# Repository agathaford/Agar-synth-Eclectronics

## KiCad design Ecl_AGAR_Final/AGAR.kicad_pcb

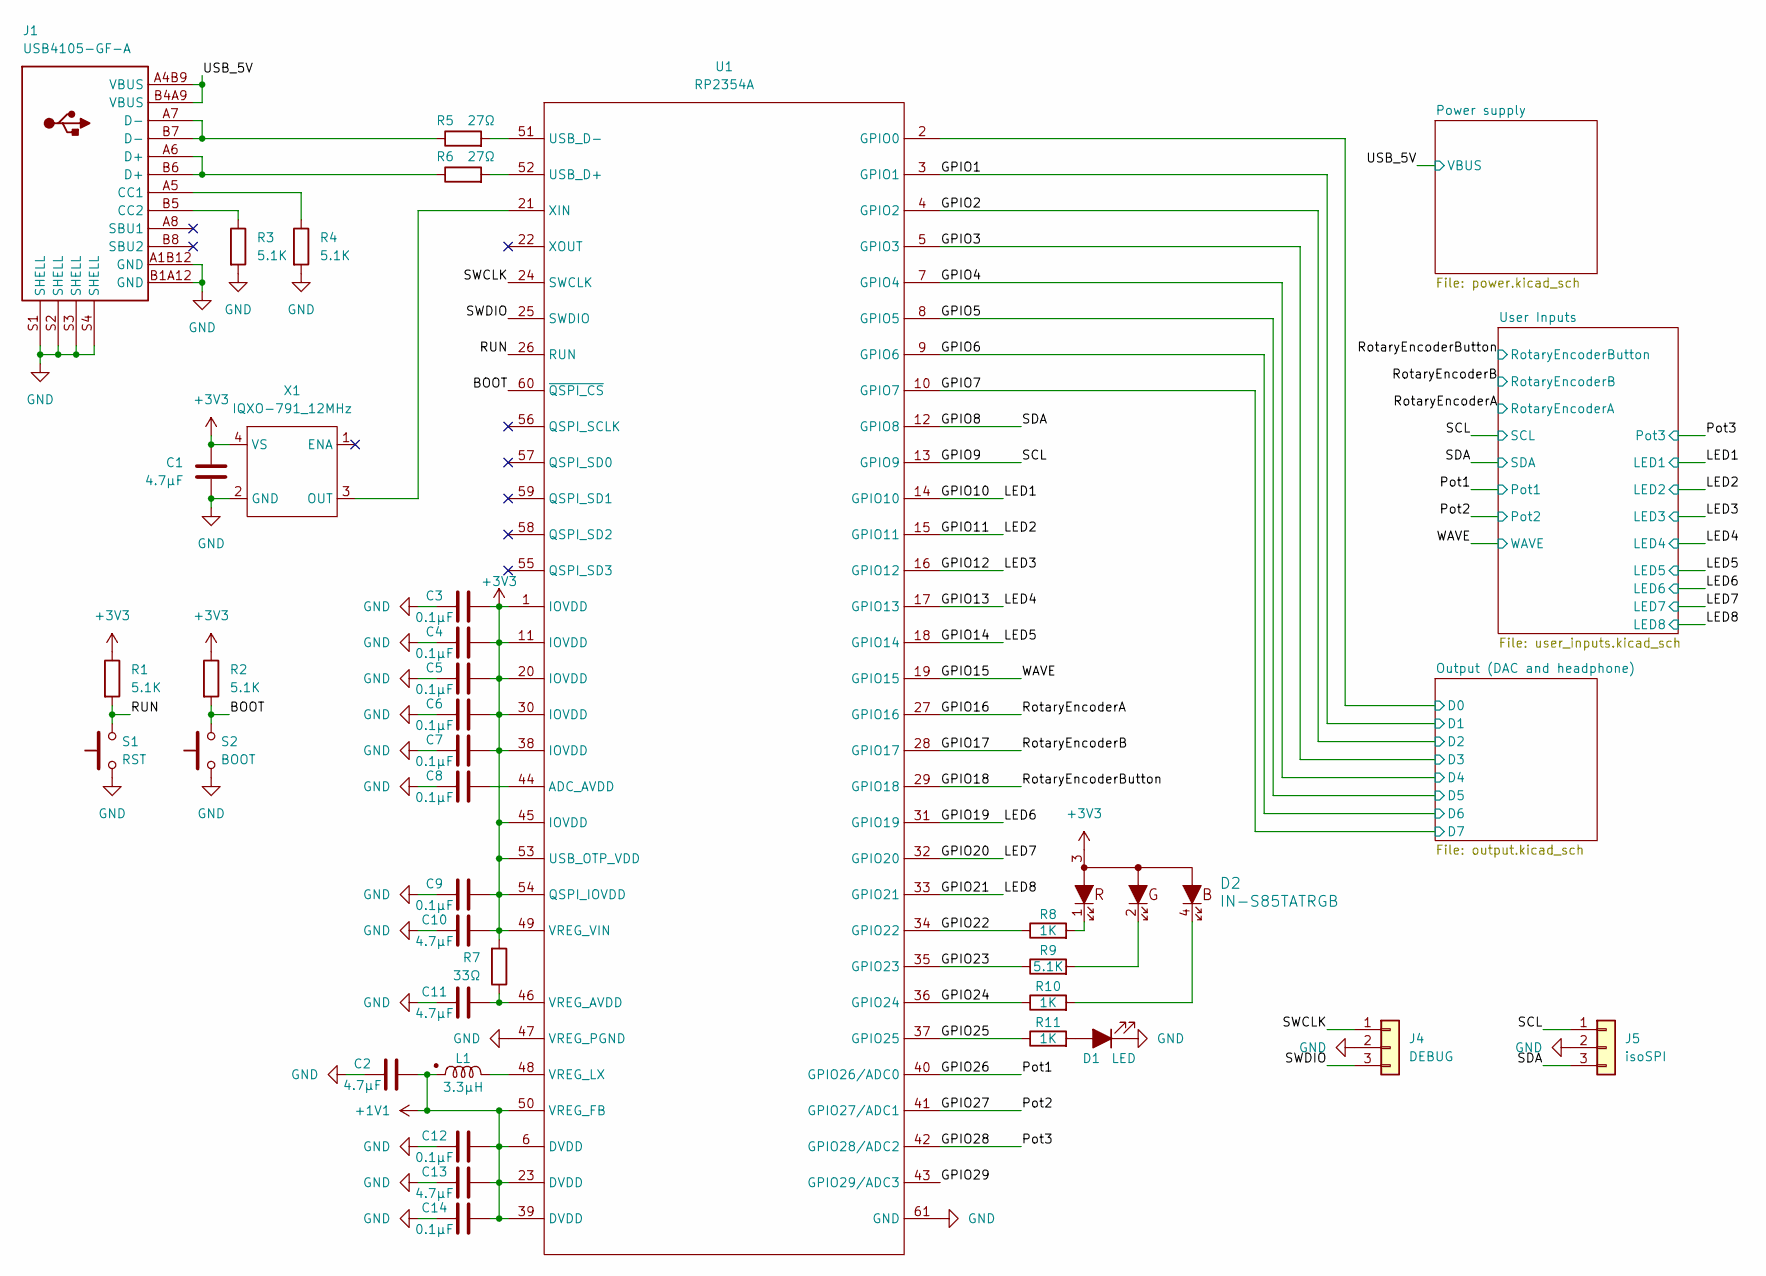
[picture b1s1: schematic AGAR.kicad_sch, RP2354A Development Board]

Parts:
C1, C2, C10, C11, C13: 4.7µF; C_0603_1608Metric
C3, C4, C5, C6, C7, C8, C9, C12, C14: 0.1µF; C_0603_1608Metric
D1: LED; LED_0805_2012Metric
D2: IN-S85TATRGB
J1: USB4105-GF-A
J4: DEBUG; PinHeader_1x03_P2.54mm_Vertical
J5: isoSPI; PinHeader_1x03_P2.54mm_Vertical
L1: 3.3µH; AOTA-B201610S3R3-101-T
R1, R2, R3, R4, R9: 5.1K; R_0603_1608Metric
R5, R6: 27Ω; R_0603_1608Metric
R7: 33Ω; R_0603_1608Metric
R8, R10, R11: 1K; R_0603_1608Metric
S1: RST; TL3301AFxxxxJ
S2: BOOT; TL3301AFxxxxJ
U1: RP2354A; RP2350A_QFN-60_EP_7.75x7.75_Pitch0.4mm
X1: IQXO-791_12MHz; WE-SPXO_IQXO-791

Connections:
+1V1: C2.2, C12.2, C13.2, C14.2, L1.1, U1.6 (DVDD), U1.23 (DVDD), U1.39 (DVDD), U1.50 (VREG_FB)
+3V3: C1.2, C3.2, C4.2, C5.2, C6.2, C7.2, C8.2, C9.2, C10.2, D2.3, R1.1, R2.1, R7.2, U1.1 (IOVDD), U1.11 (IOVDD), U1.20 (IOVDD), U1.30 (IOVDD), U1.38 (IOVDD), U1.44 (ADC_AVDD), U1.45 (IOVDD), U1.49 (VREG_VIN), U1.53 (USB_OTP_VDD), U1.54 (QSPI_IOVDD), X1.4 (VS); also elsewhere on the board
/BOOT: R2.2, S2.2, U1.60 (~QSPI_CS)
/GPIO1: U1.3 (GPIO1); also elsewhere on the board
/GPIO2: U1.4 (GPIO2); also elsewhere on the board
/GPIO3: U1.5 (GPIO3); also elsewhere on the board
/GPIO4: U1.7 (GPIO4); also elsewhere on the board
/GPIO5: U1.8 (GPIO5); also elsewhere on the board
/GPIO6: U1.9 (GPIO6); also elsewhere on the board
/GPIO7: U1.10 (GPIO7); also elsewhere on the board
/GPIO8: J5.3, U1.12 (GPIO8); also elsewhere on the board
/GPIO9: J5.1, U1.13 (GPIO9); also elsewhere on the board
/GPIO10: U1.14 (GPIO10); also elsewhere on the board
/GPIO11: U1.15 (GPIO11); also elsewhere on the board
/GPIO12: U1.16 (GPIO12); also elsewhere on the board
/GPIO13: U1.17 (GPIO13); also elsewhere on the board
/GPIO14: U1.18 (GPIO14); also elsewhere on the board
/GPIO15: U1.19 (GPIO15); also elsewhere on the board
/GPIO16: U1.27 (GPIO16); also elsewhere on the board
/GPIO17: U1.28 (GPIO17); also elsewhere on the board
/GPIO18: U1.29 (GPIO18); also elsewhere on the board
/GPIO19: U1.31 (GPIO19); also elsewhere on the board
/GPIO20: U1.32 (GPIO20); also elsewhere on the board
/GPIO21: U1.33 (GPIO21); also elsewhere on the board
/GPIO22: R8.1, U1.34 (GPIO22)
/GPIO23: R9.1, U1.35 (GPIO23)
/GPIO24: R10.1, U1.36 (GPIO24)
/GPIO25: R11.1, U1.37 (GPIO25)
/GPIO26: U1.40 (GPIO26/ADC0); also elsewhere on the board
/GPIO27: U1.41 (GPIO27/ADC1); also elsewhere on the board
/GPIO28: U1.42 (GPIO28/ADC2); also elsewhere on the board
/GPIO29: U1.43 (GPIO29/ADC3)
/Output (DAC and headphone)/D0: U1.2 (GPIO0); also elsewhere on the board
/RUN: R1.2, S1.2, U1.26 (RUN)
/SWCLK: J4.1, U1.24 (SWCLK)
/SWDIO: J4.3, U1.25 (SWDIO)
/USB_5V: J1.A4B9 (VBUS), J1.B4A9 (VBUS); also elsewhere on the board
GND: C1.1, C2.1, C3.1, C4.1, C5.1, C6.1, C7.1, C8.1, C9.1, C10.1, C11.1, C12.1, C13.1, C14.1, D1.1 (K), J1.A1B12 (GND), J1.B1A12 (GND), J1.S1 (SHELL), J1.S2 (SHELL), J1.S3 (SHELL), J1.S4 (SHELL), J4.2, J5.2, R3.2, R4.2, S1.1, S2.1, U1.47 (VREG_PGND), U1.61 (GND), X1.2 (GND); also elsewhere on the board
unnamed: D1.2 (A), R11.2
unnamed: D2.1, R8.2
unnamed: D2.2, R9.2
unnamed: D2.4, R10.2
unnamed: J1.A5 (CC1), R4.1
unnamed: J1.B5 (CC2), R3.1
unnamed: J1.A6 (D+), J1.B6 (D+), R6.1
unnamed: J1.A7 (D-), J1.B7 (D-), R5.1
unnamed: R6.2, U1.52 (USB_D+)
unnamed: R5.2, U1.51 (USB_D-)
unnamed: C11.2, R7.1, U1.46 (VREG_AVDD)
unnamed: L1.2, U1.48 (VREG_LX)
unnamed: U1.21 (XIN), X1.3 (OUT)

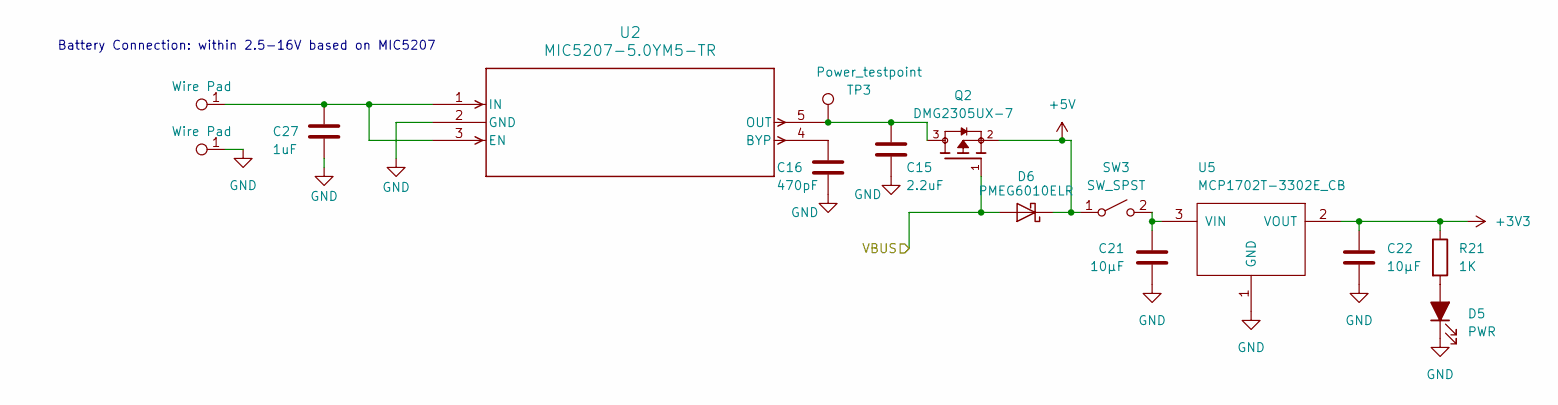
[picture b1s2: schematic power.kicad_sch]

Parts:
C15: 2.2uF; C_0603_1608Metric
C16: 470pF; C_0603_1608Metric
C21, C22: 10µF; C_0603_1608Metric
C27: 1uF; C_0603_1608Metric
D5: PWR; LED_0805_2012Metric
D6: PMEG6010ELR; Nexperia_CFP3_SOD-123W
Q2: DMG2305UX-7; DMG2305UX_7_SOT-23_DIO; MPN DMG2305UX-7
R21: 1K; R_0603_1608Metric
SW3: SW_SPST; SLW-1276864_CUD
TP3: Power_testpoint; TestPoint_Pad_D3.0mm
U2: MIC5207-5.0YM5-TR; SOT-23-5_M5_MCH
U5: MCP1702T-3302E_CB; SOT95P255X145-3N
WirePad13, WirePad14: Wire Pad

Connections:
+3V3: C22.1, R21.1, U5.2 (VOUT); also elsewhere on the board
+5V: D6.1 (K), Q2.2, SW3.1 (A); also elsewhere on the board
/USB_5V: D6.2 (A), Q2.1; also elsewhere on the board
GND: C15.2, C16.2, C21.1, C22.2, C27.2, D5.1 (K), U2.2 (GND), U5.1 (GND), WirePad14.1 (1_1); also elsewhere on the board
unnamed: D5.2 (A), R21.2
unnamed: C21.2, SW3.2 (B), U5.3 (VIN)
unnamed: C16.1, U2.4 (BYP)
unnamed: C27.1, U2.1 (IN), U2.3 (EN), WirePad13.1 (1_1)
unnamed: C15.1, Q2.3, TP3.1 (1_1), U2.5 (OUT)

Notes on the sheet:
Battery Connection: within 2.5-16V based on MIC5207

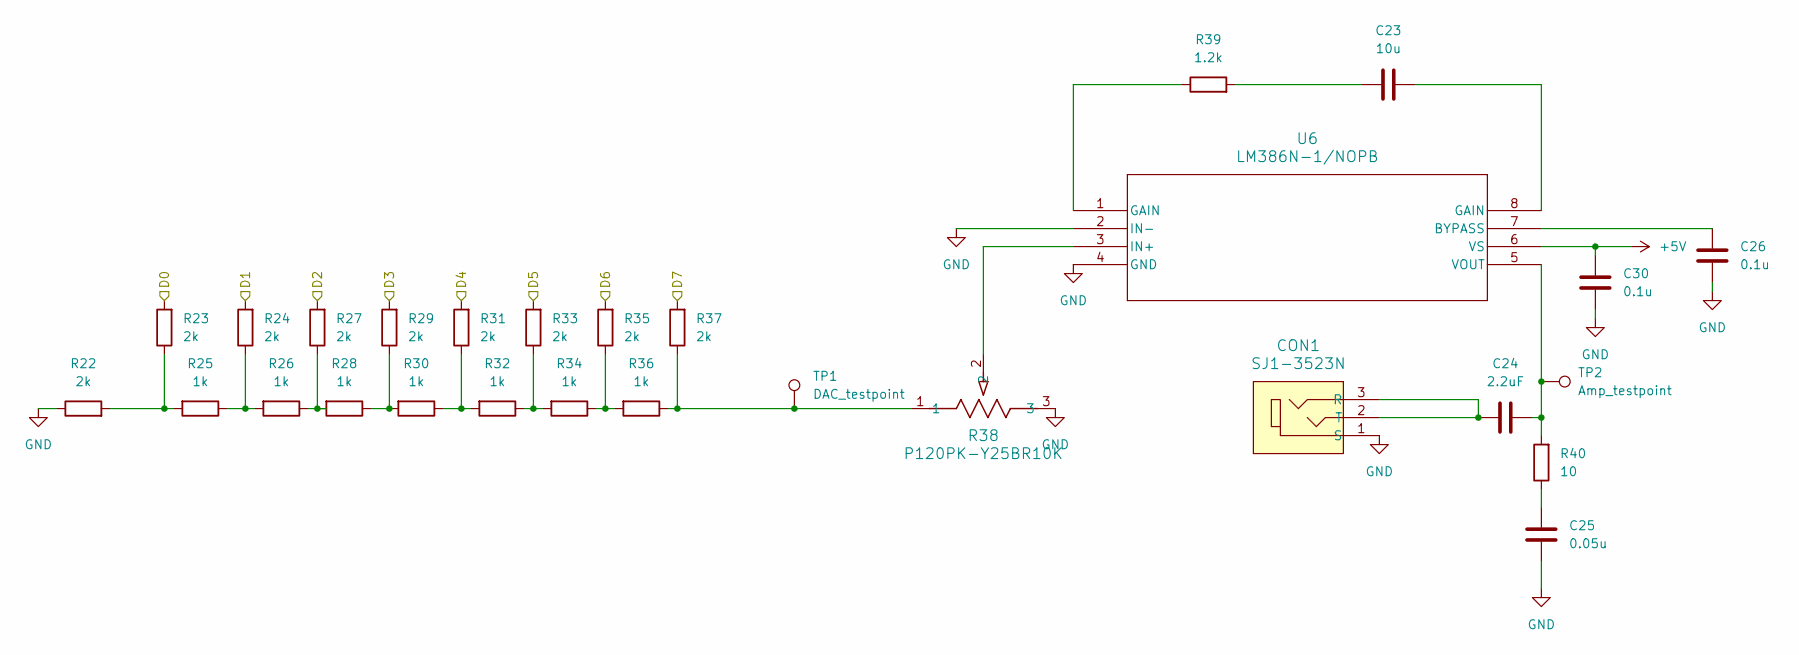
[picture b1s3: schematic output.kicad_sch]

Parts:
C23: 10u; C_0603_1608Metric
C24: 2.2uF; C_0603_1608Metric
C25: 0.05u; C_1206_3216Metric
C26, C30: 0.1u; C_0603_1608Metric
CON1: SJ1-3523N; Jack_3.5mm_CUI_SJ-3523-SMT_Horizontal; MPN SJ1-3523N; Digi-Key_PN CP1-3523N-ND
R22, R23, R24, R27, R29, R31, R33, R35, R37: 2k; R_0603_1608Metric
R25, R26, R28, R30, R32, R34, R36: 1k; R_0603_1608Metric
R38: P120PK-Y25BR10K; Potentiometer_Bourns_3386F_Vertical
R39: 1.2k; R_0603_1608Metric
R40: 10; R_0603_1608Metric
TP1: DAC_testpoint; TestPoint_Pad_D3.0mm
TP2: Amp_testpoint; TestPoint_Pad_D3.0mm
U6: LM386N-1/NOPB; AMP_to_speaker

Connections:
+5V: C30.2, U6.6 (VS); also elsewhere on the board
/GPIO1: R24.2; also elsewhere on the board
/GPIO2: R27.2; also elsewhere on the board
/GPIO3: R29.2; also elsewhere on the board
/GPIO4: R31.2; also elsewhere on the board
/GPIO5: R33.2; also elsewhere on the board
/GPIO6: R35.2; also elsewhere on the board
/GPIO7: R37.2; also elsewhere on the board
/Output (DAC and headphone)/D0: R23.2; also elsewhere on the board
GND: C25.1, C26.1, C30.1, CON1.1 (S), R22.1, R38.3, U6.2 (IN-), U6.4 (GND); also elsewhere on the board
unnamed: C23.1, R39.2
unnamed: C23.2, U6.8 (GAIN)
unnamed: C25.2, R40.1
unnamed: C24.2, CON1.2 (T), CON1.3 (R)
unnamed: R22.2, R23.1, R25.2
unnamed: R24.1, R25.1, R26.2
unnamed: R26.1, R27.1, R28.2
unnamed: R28.1, R29.1, R30.2
unnamed: R30.1, R31.1, R32.2
unnamed: R32.1, R33.1, R34.2
unnamed: R34.1, R35.1, R36.2
unnamed: R36.1, R37.1, R38.1, TP1.1 (1_1)
unnamed: R39.1, U6.1 (GAIN)
unnamed: C26.2, U6.7 (BYPASS)
unnamed: R38.2, U6.3 (IN+)
unnamed: C24.1, R40.2, TP2.1 (1_1), U6.5 (VOUT)

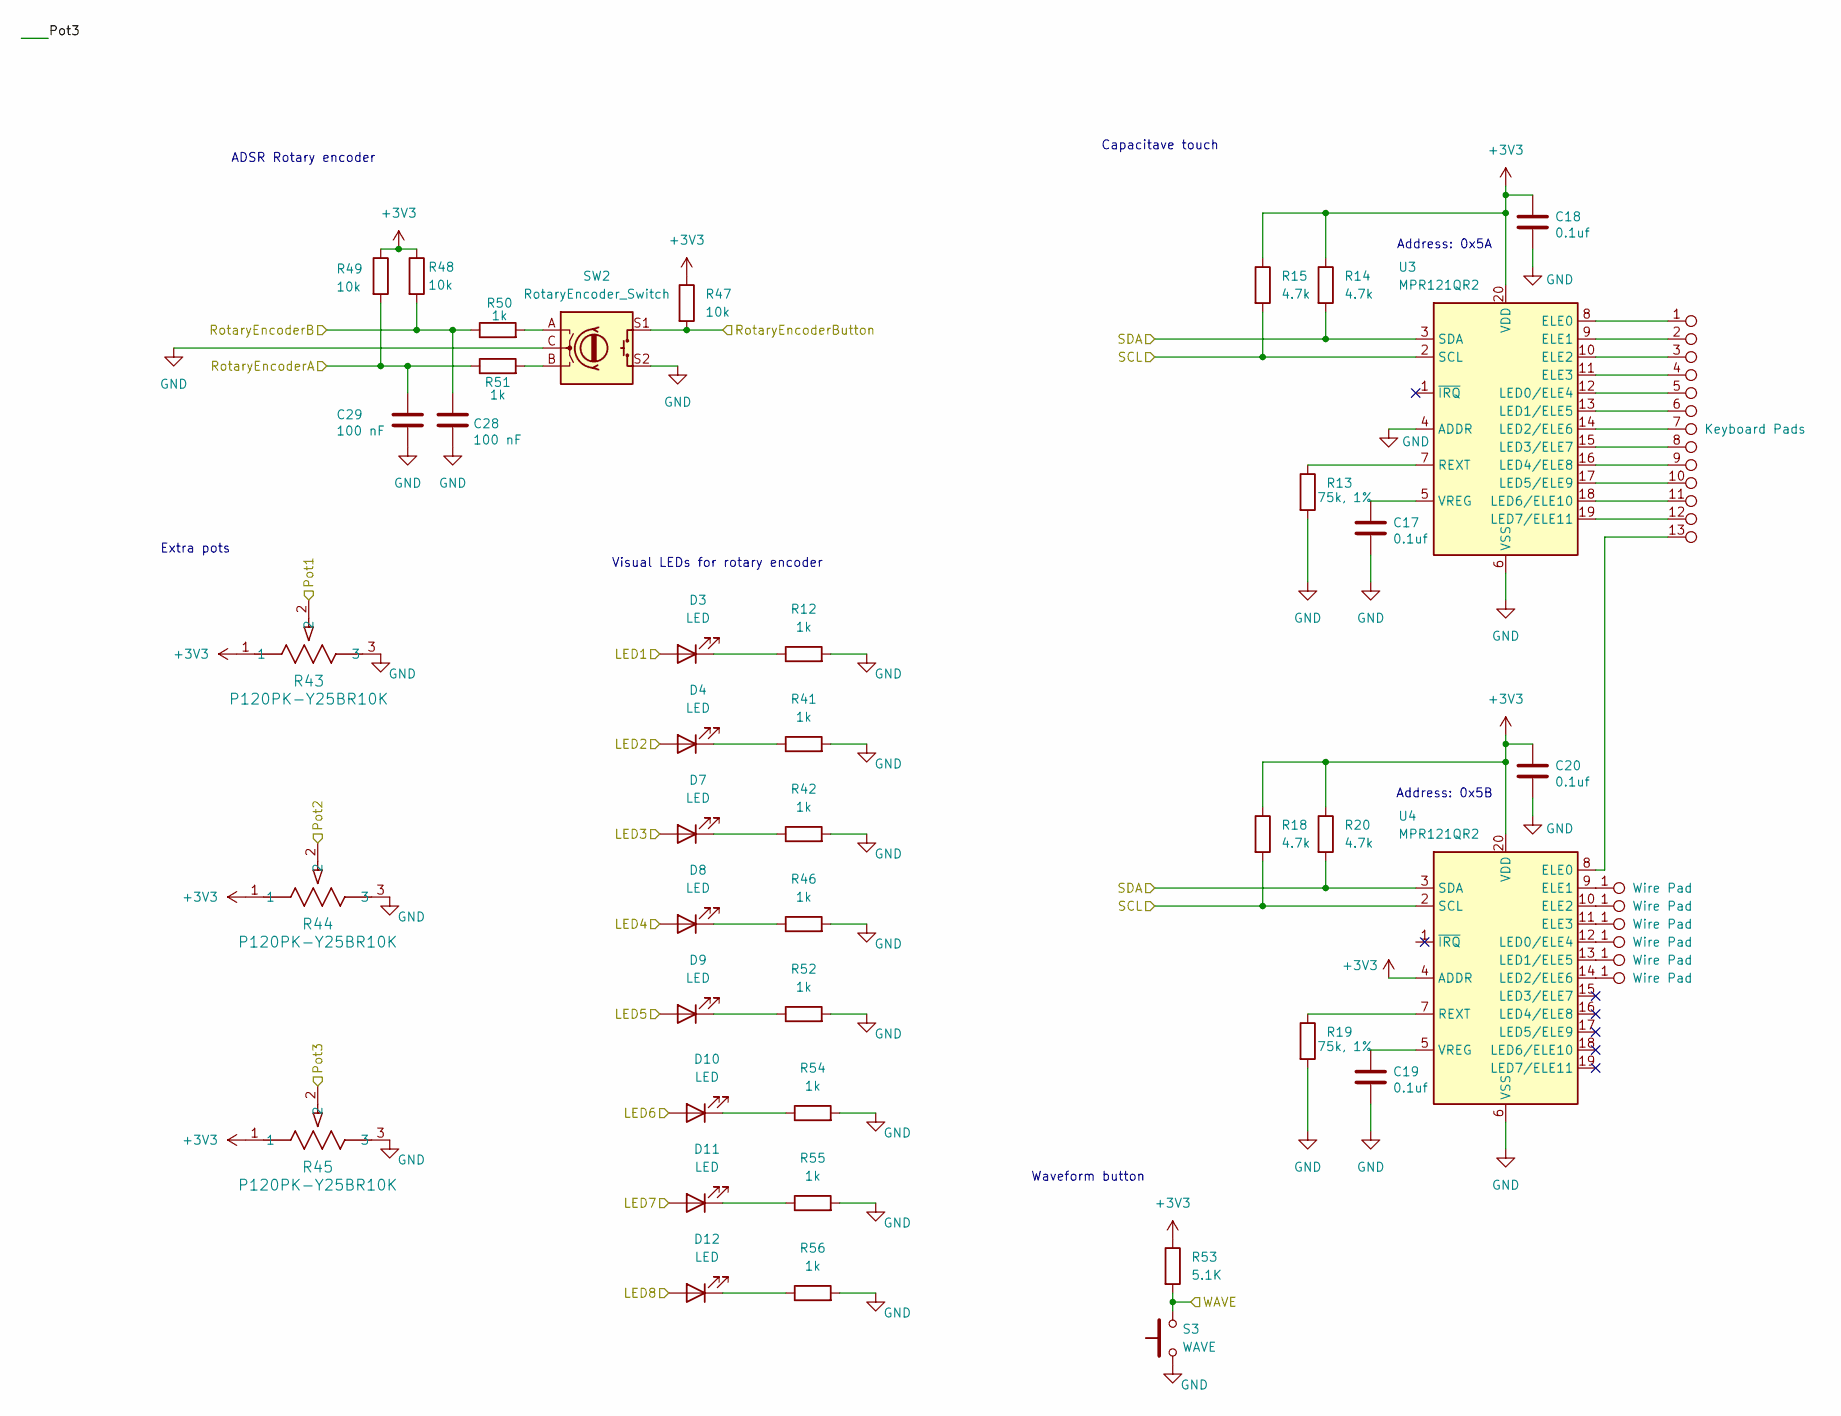
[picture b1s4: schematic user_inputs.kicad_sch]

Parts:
C17, C18, C19, C20: 0.1uf; C_0603_1608Metric
C28, C29: 100 nF; C_0603_1608Metric
D3, D4, D7, D8, D9, D10, D11, D12: LED; LED_0603_1608Metric_Pad1.05x0.95mm_HandSolder
R12, R41, R42, R46, R50, R51, R52, R54, R55, R56: 1k; R_0603_1608Metric
R13, R19: 75k, 1%; R_0603_1608Metric
R14, R15, R18, R20: 4.7k; R_0603_1608Metric
R43, R44, R45: P120PK-Y25BR10K; Potentiometer_Bourns_3386F_Vertical
R47, R48, R49: 10k; R_0603_1608Metric
R53: 5.1K; R_0603_1608Metric
S3: WAVE; TL3301AFxxxxJ
SW2: RotaryEncoder_Switch; EC11E18244A5_ALPS
U3, U4: MPR121QR2; UQFN-20_3x3mm_P0.4mm
WirePad3: Keyboard Pads; capacitive touch keyboard
WirePad4, WirePad5, WirePad6, WirePad7, WirePad8, WirePad9: Wire Pad; capacitive touch button

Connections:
+3V3: C18.1, C20.1, R14.1, R15.1, R18.1, R20.1, R43.1, R44.1, R45.1, R47.1, R48.1, R49.1, R53.1, U3.20 (VDD), U4.4 (ADDR), U4.20 (VDD); also elsewhere on the board
/GPIO8: R14.2, R20.2, U3.3 (SDA), U4.3 (SDA); also elsewhere on the board
/GPIO9: R15.2, R18.2, U3.2 (SCL), U4.2 (SCL); also elsewhere on the board
/GPIO10: D3.2 (A); also elsewhere on the board
/GPIO11: D4.2 (A); also elsewhere on the board
/GPIO12: D7.2 (A); also elsewhere on the board
/GPIO13: D8.2 (A); also elsewhere on the board
/GPIO14: D9.2 (A); also elsewhere on the board
/GPIO15: R53.2, S3.2; also elsewhere on the board
/GPIO16: C29.1, R49.2, R51.1; also elsewhere on the board
/GPIO17: C28.1, R48.2, R50.1; also elsewhere on the board
/GPIO18: R47.2, SW2.S1; also elsewhere on the board
/GPIO19: D10.2 (A); also elsewhere on the board
/GPIO20: D11.2 (A); also elsewhere on the board
/GPIO21: D12.2 (A); also elsewhere on the board
/GPIO26: R43.2; also elsewhere on the board
/GPIO27: R44.2; also elsewhere on the board
/GPIO28: R45.2; also elsewhere on the board
GND: C17.2, C18.2, C19.2, C20.2, C28.2, C29.2, R12.2, R13.2, R19.2, R41.2, R42.2, R43.3, R44.3, R45.3, R46.2, R52.2, R54.2, R55.2, R56.2, S3.1, SW2.C, SW2.S2, U3.4 (ADDR), U3.6 (VSS), U4.6 (VSS); also elsewhere on the board
unnamed: D3.1 (K), R12.1
unnamed: D4.1 (K), R41.1
unnamed: D7.1 (K), R42.1
unnamed: D8.1 (K), R46.1
unnamed: D9.1 (K), R52.1
unnamed: D10.1 (K), R54.1
unnamed: D11.1 (K), R55.1
unnamed: D12.1 (K), R56.1
unnamed: R50.2, SW2.A
unnamed: R51.2, SW2.B
unnamed: U3.8 (ELE0), WirePad3.1
unnamed: U3.9 (ELE1), WirePad3.2
unnamed: U3.10 (ELE2), WirePad3.3
unnamed: U3.11 (ELE3), WirePad3.4
unnamed: U3.12 (LED0/ELE4), WirePad3.5
unnamed: U3.13 (LED1/ELE5), WirePad3.6
unnamed: U3.14 (LED2/ELE6), WirePad3.7
unnamed: U3.15 (LED3/ELE7), WirePad3.8
unnamed: U3.16 (LED4/ELE8), WirePad3.9
unnamed: U3.17 (LED5/ELE9), WirePad3.10
unnamed: U3.18 (LED6/ELE10), WirePad3.11
unnamed: U3.19 (LED7/ELE11), WirePad3.12
unnamed: R13.1, U3.7 (REXT)
unnamed: C17.1, U3.5 (VREG)
unnamed: U4.8 (ELE0), WirePad3.13
unnamed: U4.9 (ELE1), WirePad4.1 (1_1)
unnamed: U4.10 (ELE2), WirePad5.1 (1_1)
unnamed: U4.11 (ELE3), WirePad6.1 (1_1)
unnamed: U4.12 (LED0/ELE4), WirePad7.1 (1_1)
unnamed: U4.13 (LED1/ELE5), WirePad8.1 (1_1)
unnamed: U4.14 (LED2/ELE6), WirePad9.1 (1_1)
unnamed: R19.1, U4.7 (REXT)
unnamed: C19.1, U4.5 (VREG)

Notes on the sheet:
Address: 0x5A
ADSR Rotary encoder
Visual LEDs for rotary encoder
Capacitave touch
Extra pots
Address: 0x5B
Waveform button

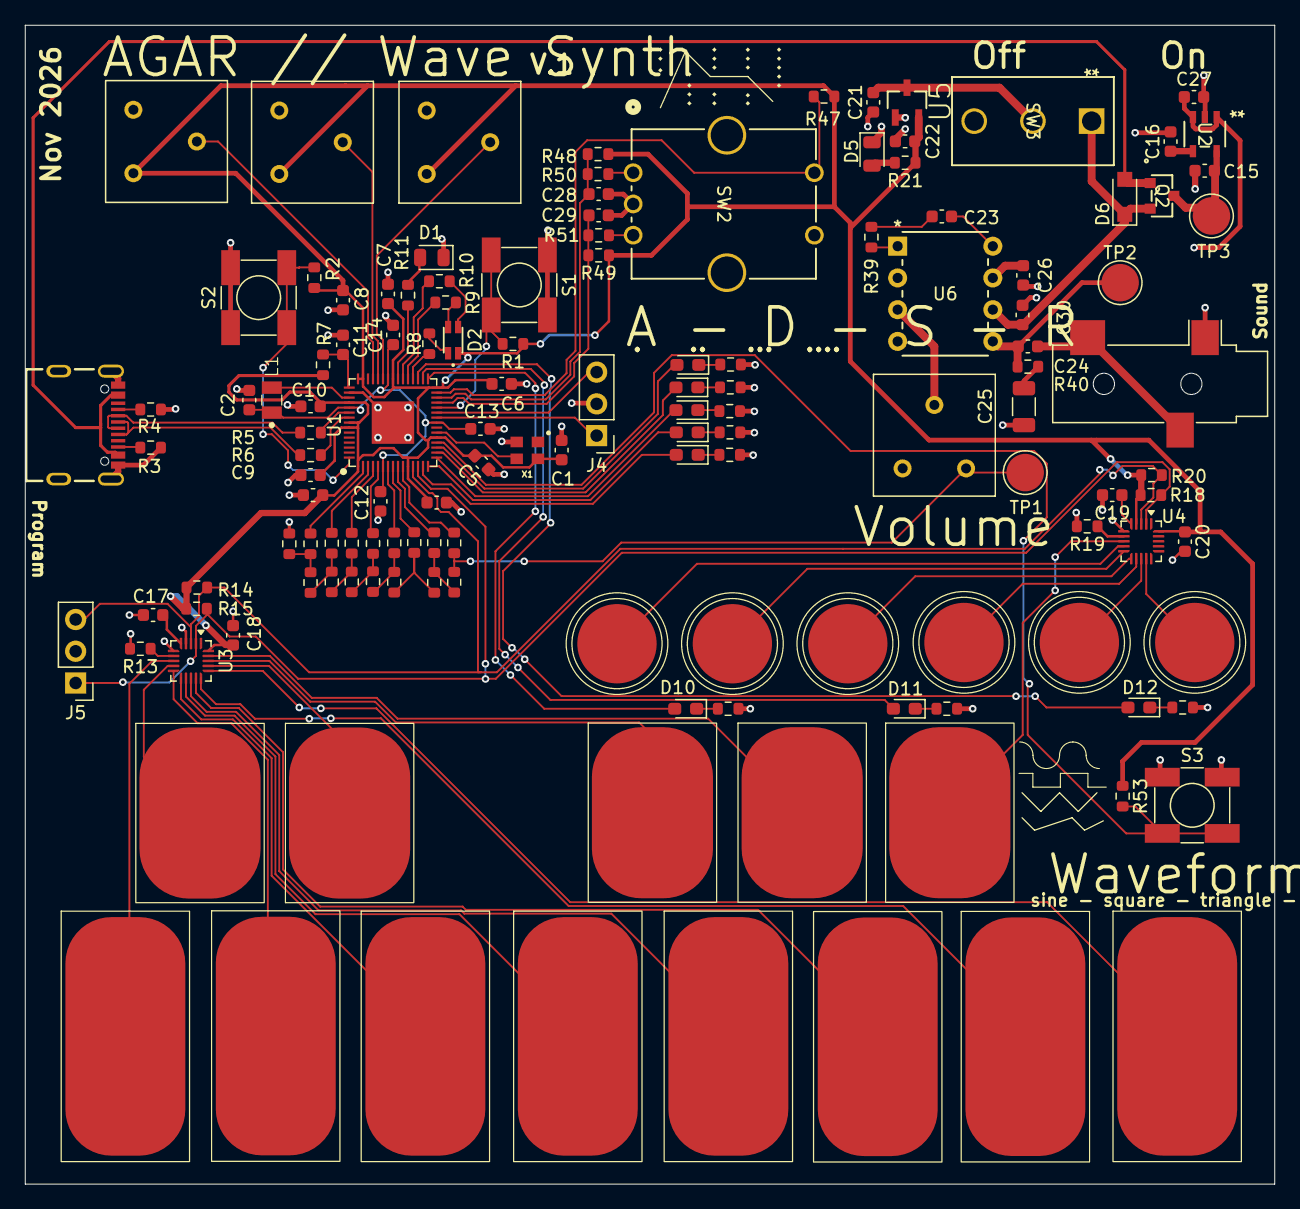
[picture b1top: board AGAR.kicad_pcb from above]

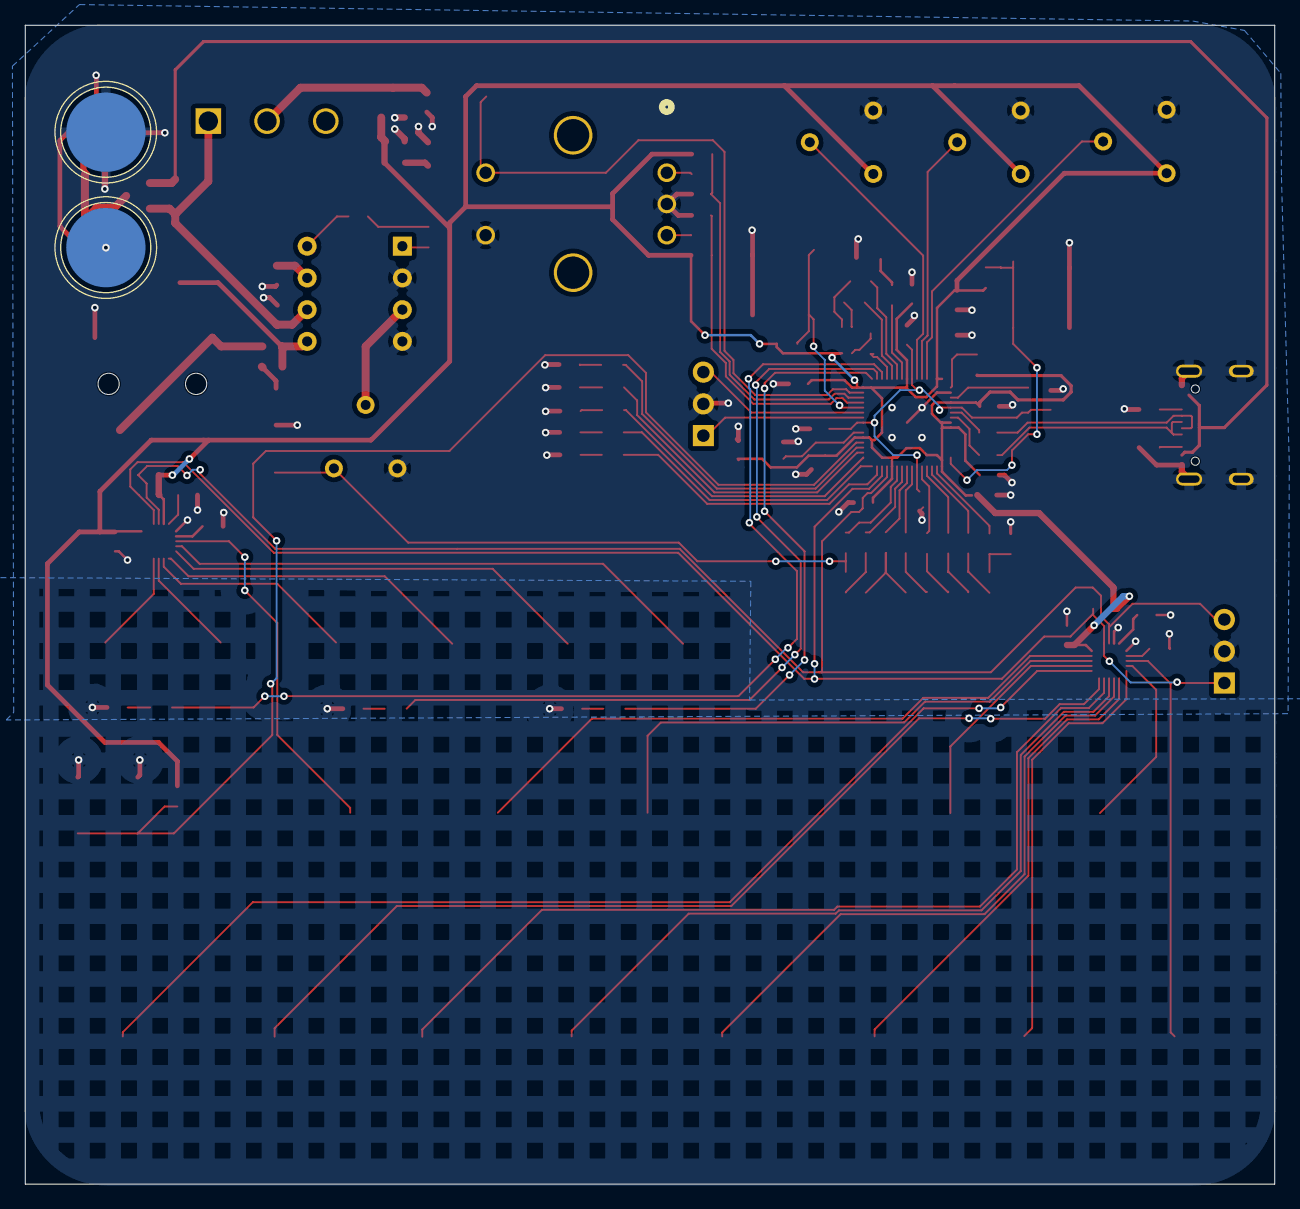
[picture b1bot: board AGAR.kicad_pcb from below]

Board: 2 copper layers, 100.0 x 92.8 mm, 126 parts (2 on the bottom side), 105 nets.

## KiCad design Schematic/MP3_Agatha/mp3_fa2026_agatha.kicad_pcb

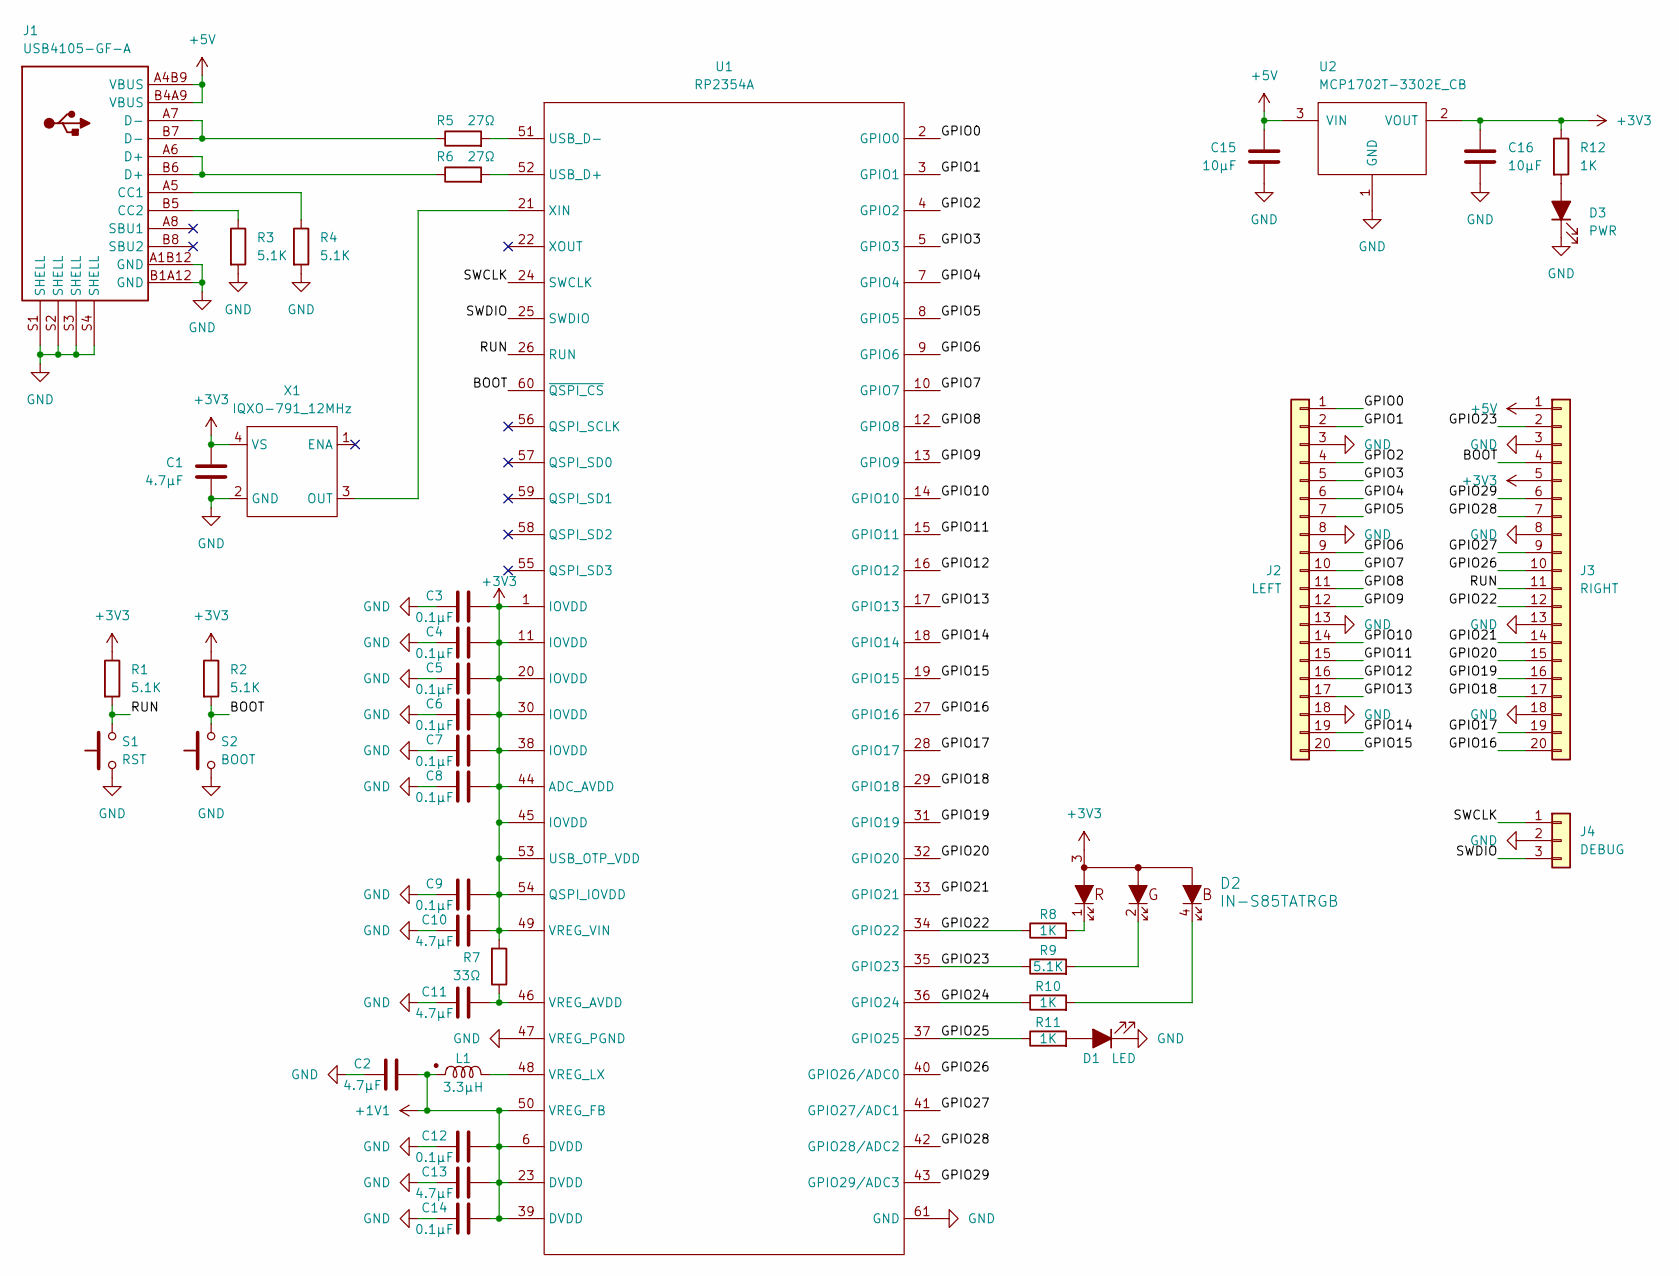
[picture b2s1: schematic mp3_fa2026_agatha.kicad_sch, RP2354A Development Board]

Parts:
C1, C2, C10, C11, C13: 4.7µF; C_0603_1608Metric
C3, C4, C5, C6, C7, C8, C9, C12, C14: 0.1µF; C_0603_1608Metric
C15, C16: 10µF; C_0603_1608Metric
D1: LED; LED_0805_2012Metric
D2: IN-S85TATRGB
D3: PWR; LED_0805_2012Metric
J1: USB4105-GF-A
J2: LEFT; PinHeader_1x20_P2.54mm_Vertical
J3: RIGHT; PinHeader_1x20_P2.54mm_Vertical
J4: DEBUG; PinHeader_1x03_P2.54mm_Vertical
L1: 3.3µH; AOTA-B201610S3R3-101-T
R1, R2, R3, R4, R9: 5.1K; R_0603_1608Metric
R5, R6: 27Ω; R_0603_1608Metric
R7: 33Ω; R_0603_1608Metric
R8, R10, R11, R12: 1K; R_0603_1608Metric
S1: RST; TL3301AFxxxxJ
S2: BOOT; TL3301AFxxxxJ
U1: RP2354A; RP2350A_QFN-60_EP_7.75x7.75_Pitch0.4mm
U2: MCP1702T-3302E_CB; SOT-23-8
X1: IQXO-791_12MHz; WE-SPXO_IQXO-791

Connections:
+1V1: C2.2, C12.2, C13.2, C14.2, L1.1, U1.6 (DVDD), U1.23 (DVDD), U1.39 (DVDD), U1.50 (VREG_FB)
+3V3: C1.2, C3.2, C4.2, C5.2, C6.2, C7.2, C8.2, C9.2, C10.2, C16.1, D2.3, J3.5, R1.1, R2.1, R7.2, R12.1, U1.1 (IOVDD), U1.11 (IOVDD), U1.20 (IOVDD), U1.30 (IOVDD), U1.38 (IOVDD), U1.44 (ADC_AVDD), U1.45 (IOVDD), U1.49 (VREG_VIN), U1.53 (USB_OTP_VDD), U1.54 (QSPI_IOVDD), U2.2 (VOUT), X1.4 (VS)
+5V: C15.2, J1.A4B9 (VBUS), J1.B4A9 (VBUS), J3.1, U2.3 (VIN)
/BOOT: J3.4, R2.2, S2.2, U1.60 (~QSPI_CS)
/GPIO0: J2.1, U1.2 (GPIO0)
/GPIO1: J2.2, U1.3 (GPIO1)
/GPIO2: J2.4, U1.4 (GPIO2)
/GPIO3: J2.5, U1.5 (GPIO3)
/GPIO4: J2.6, U1.7 (GPIO4)
/GPIO5: J2.7, U1.8 (GPIO5)
/GPIO6: J2.9, U1.9 (GPIO6)
/GPIO7: J2.10, U1.10 (GPIO7)
/GPIO8: J2.11, U1.12 (GPIO8)
/GPIO9: J2.12, U1.13 (GPIO9)
/GPIO10: J2.14, U1.14 (GPIO10)
/GPIO11: J2.15, U1.15 (GPIO11)
/GPIO12: J2.16, U1.16 (GPIO12)
/GPIO13: J2.17, U1.17 (GPIO13)
/GPIO14: J2.19, U1.18 (GPIO14)
/GPIO15: J2.20, U1.19 (GPIO15)
/GPIO16: J3.20, U1.27 (GPIO16)
/GPIO17: J3.19, U1.28 (GPIO17)
/GPIO18: J3.17, U1.29 (GPIO18)
/GPIO19: J3.16, U1.31 (GPIO19)
/GPIO20: J3.15, U1.32 (GPIO20)
/GPIO21: J3.14, U1.33 (GPIO21)
/GPIO22: J3.12, R8.1, U1.34 (GPIO22)
/GPIO23: J3.2, R9.1, U1.35 (GPIO23)
/GPIO24: R10.1, U1.36 (GPIO24)
/GPIO25: R11.1, U1.37 (GPIO25)
/GPIO26: J3.10, U1.40 (GPIO26/ADC0)
/GPIO27: J3.9, U1.41 (GPIO27/ADC1)
/GPIO28: J3.7, U1.42 (GPIO28/ADC2)
/GPIO29: J3.6, U1.43 (GPIO29/ADC3)
/RUN: J3.11, R1.2, S1.2, U1.26 (RUN)
/SWCLK: J4.1, U1.24 (SWCLK)
/SWDIO: J4.3, U1.25 (SWDIO)
GND: C1.1, C2.1, C3.1, C4.1, C5.1, C6.1, C7.1, C8.1, C9.1, C10.1, C11.1, C12.1, C13.1, C14.1, C15.1, C16.2, D1.1 (K), D3.1 (K), J1.A1B12 (GND), J1.B1A12 (GND), J1.S1 (SHELL), J1.S2 (SHELL), J1.S3 (SHELL), J1.S4 (SHELL), J2.3, J2.8, J2.13, J2.18, J3.3, J3.8, J3.13, J3.18, J4.2, R3.2, R4.2, S1.1, S2.1, U1.47 (VREG_PGND), U1.61 (GND), U2.1 (GND), X1.2 (GND)
unnamed: D1.2 (A), R11.2
unnamed: D2.1, R8.2
unnamed: D2.2, R9.2
unnamed: D2.4, R10.2
unnamed: D3.2 (A), R12.2
unnamed: J1.A5 (CC1), R4.1
unnamed: J1.B5 (CC2), R3.1
unnamed: J1.A6 (D+), J1.B6 (D+), R6.1
unnamed: J1.A7 (D-), J1.B7 (D-), R5.1
unnamed: R6.2, U1.52 (USB_D+)
unnamed: R5.2, U1.51 (USB_D-)
unnamed: C11.2, R7.1, U1.46 (VREG_AVDD)
unnamed: L1.2, U1.48 (VREG_LX)
unnamed: U1.21 (XIN), X1.3 (OUT)

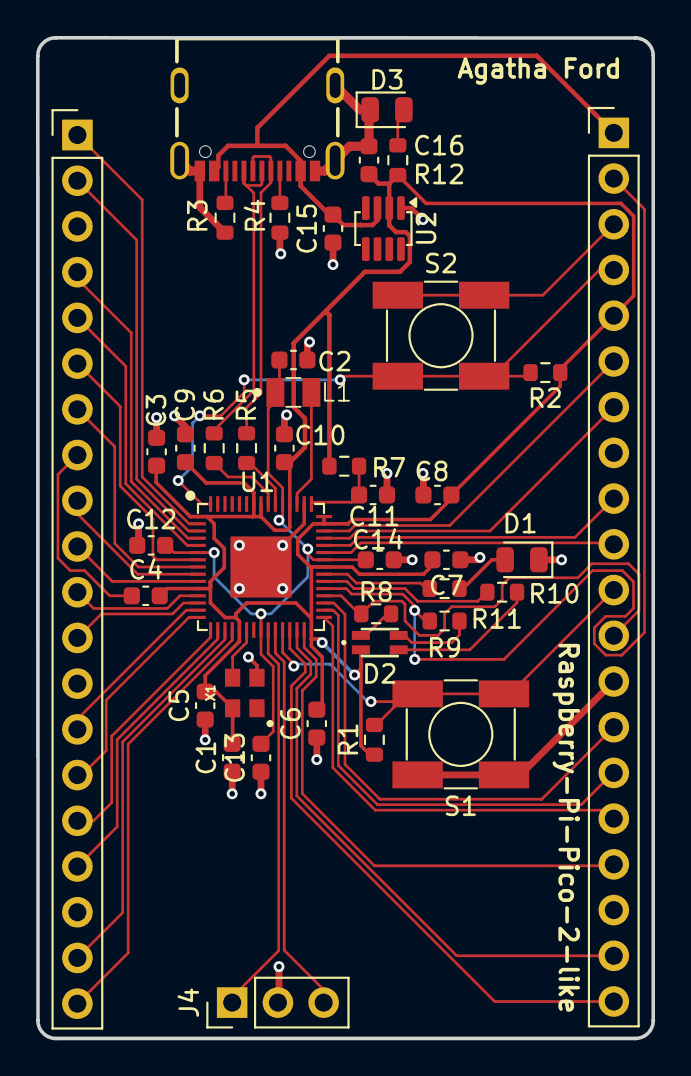
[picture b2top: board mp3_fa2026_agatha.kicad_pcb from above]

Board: 2 copper layers, 34.2 x 55.6 mm, 41 parts (0 on the bottom side), 52 nets.
